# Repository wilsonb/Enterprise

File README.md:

Enterprise
==========

Board and Arduino/ATTINY Code for Enterprise Model Lights

SMD Version Mouser BOM:

http://www.mouser.com/ProjectManager/ProjectDetail.aspx?AccessID=15ff481517

Through Hole Mouser BOM:

http://www.mouser.com/ProjectManager/ProjectDetail.aspx?AccessID=0c87d410ad

Using the .ZIP files, order the boards from http://OSHpark.com

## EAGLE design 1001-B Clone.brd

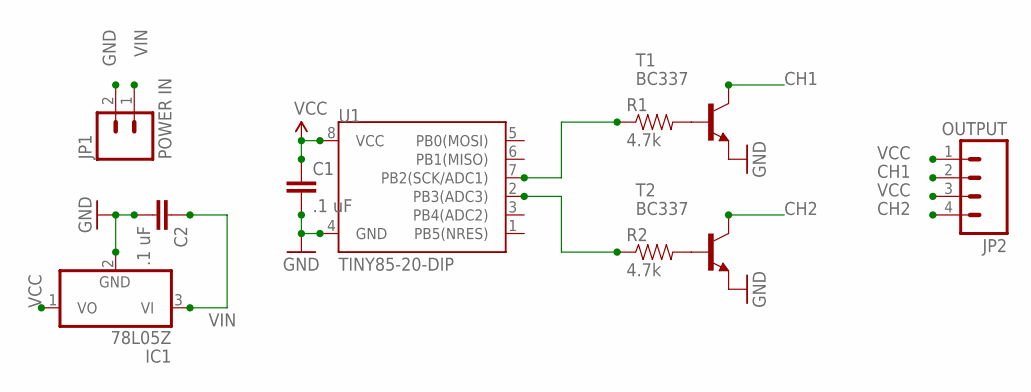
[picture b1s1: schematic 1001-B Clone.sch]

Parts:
C1, C2: .1 uF; 1206
IC1: 78L05Z; TO92
JP1: POWER IN; SCREWTERMINAL-3.5MM-2
JP2: OUTPUT; SCREWTERMINAL-3.5MM-4
R1, R2: 4.7k; 1206
T1, T2: BC337; TO92
U1: TINY85-20-DIP; DIP08

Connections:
CH1: JP2.2, T1.3 (C)
CH2: JP2.4, T2.3 (C)
GND: C1.2, C2.2, IC1.2 (GND), JP1.2, T1.1 (E), T2.1 (E), U1.4 (GND)
unnamed: R1.2, T1.2 (B)
unnamed: R2.2, T2.2 (B)
unnamed: R1.1, U1.7 (PB2(SCK/ADC1))
unnamed: R2.1, U1.2 (PB3(ADC3))
VCC: C1.1, IC1.1 (VO), JP2.1, JP2.3, U1.8 (VCC)
VIN: C2.1, IC1.3 (VI), JP1.1

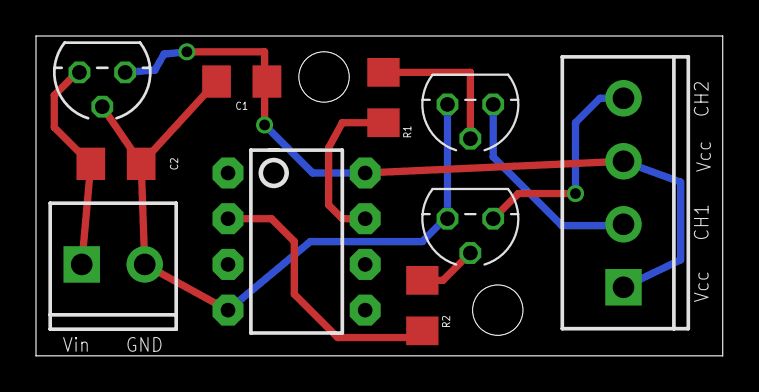
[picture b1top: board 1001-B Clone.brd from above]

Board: 2 copper layers, 38.2 x 17.8 mm, 10 parts (0 on the bottom side), 9 nets.

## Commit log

2013-06-07 new zip

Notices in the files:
parts and their libraries:
SparkFun-DigitalIC: Licensing: CC v3.0 Share-Alike You are welcome to use this library for commercial purposes.
